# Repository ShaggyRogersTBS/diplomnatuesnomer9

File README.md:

# Дипломен Проект
Разработка на метеорологична система с уеб приложение и устройство на базата на ESP32, което измерва метеорологични стойности и ги записва в база данни, откъде после те са достъпни чрез уеб приложение

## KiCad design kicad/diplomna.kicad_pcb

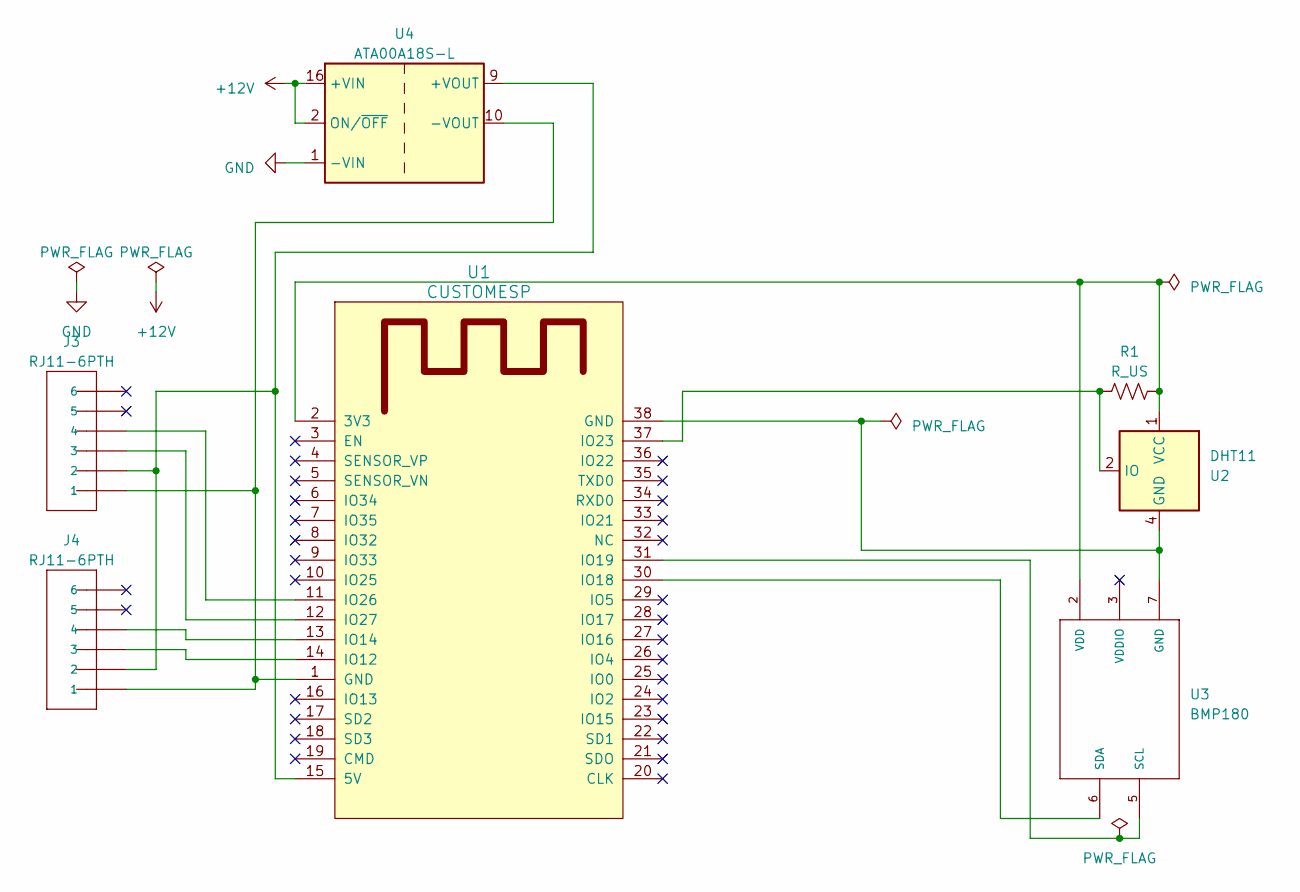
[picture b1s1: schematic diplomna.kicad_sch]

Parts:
J3, J4: RJ11-6PTH; RJ11-6
R1: R_US; R_Axial_DIN0204_L3.6mm_D1.6mm_P2.54mm_Vertical
U1: CUSTOMESP; ESP32-WROOM
U2: DHT11; Aosong_DHT11_5.5x12.0_P2.54mm
U3: BMP180
U4: ATA00A18S-L; Converter_DCDC_Artesyn_ATA_SMD

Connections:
+12V: U4.2 (ON/~OFF), U4.16 (+VIN)
GND: U4.1 (-VIN)
unnamed: R1.2, U1.2 (3V3), U2.1 (VCC), U3.2 (VDD)
unnamed: J3.2, J4.2, U1.15 (5V), U4.9 (+VOUT)
unnamed: J4.3, U1.14 (IO12)
unnamed: J4.4, U1.13 (IO14)
unnamed: U1.30 (IO18), U3.6 (SDA)
unnamed: U1.31 (IO19), U3.5 (SCL)
unnamed: R1.1, U1.37 (IO23), U2.2 (IO)
unnamed: J3.4, U1.11 (IO26)
unnamed: J3.3, U1.12 (IO27)
unnamed: U1.38 (GND), U2.4 (GND), U3.7 (GND)
unnamed: J3.1, J4.1, U1.1 (GND), U4.10 (-VOUT)

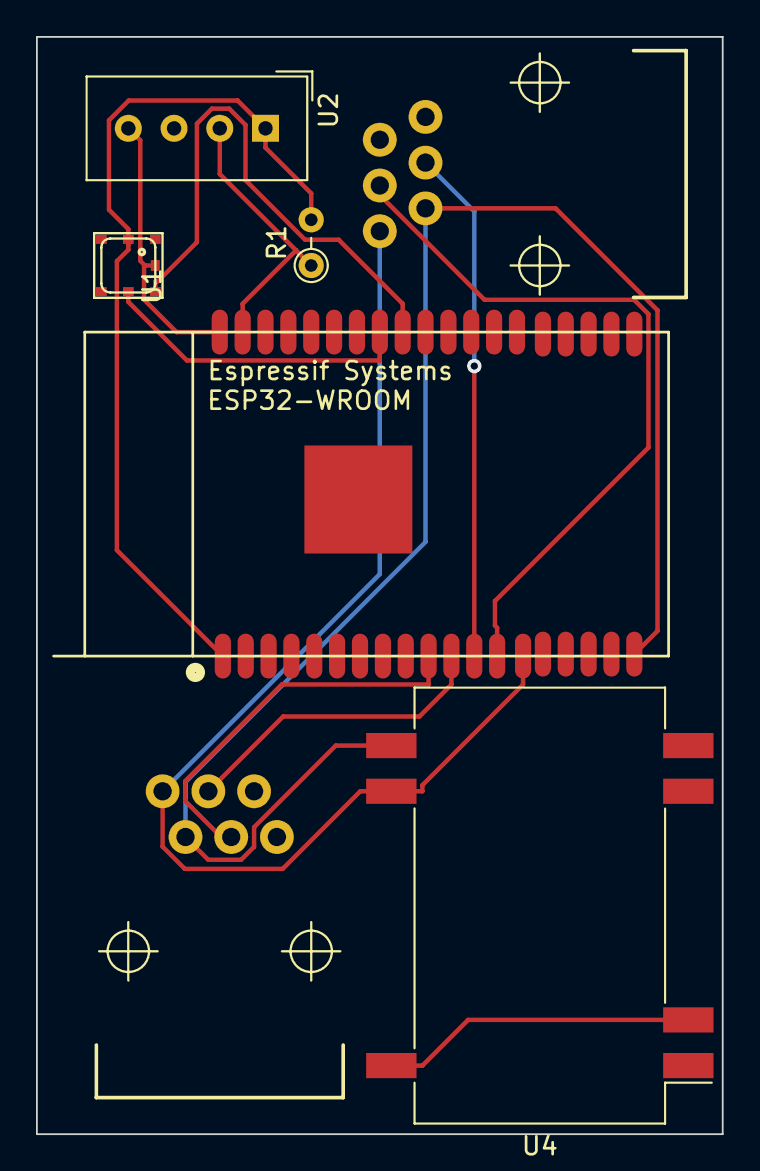
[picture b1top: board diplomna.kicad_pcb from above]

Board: 2 copper layers, 38.1 x 61.0 mm, 7 parts (0 on the bottom side), 12 nets.

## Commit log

2023-02-20 Main Page That Redirects to the next page.
2023-02-20 Rename index.php to website/index.php
2023-02-20 Rename styles.css to website/styles.css
2023-02-20 Create foldermaker
2023-02-21 css for the tables page + bootstrap install
    background photo upload
2023-03-05 added wind_direction
2023-03-05 Rename test.c to main.c
2023-03-05 wind speed query
2023-03-06 Rename diplomna.dsn to kicad/diplomna.dsn
2023-03-06 kicad pcb + schematic files
    no libraries !!!!
2023-03-07 Create httprequestsql
2023-03-07 support for wind speed, wind direction, humidity
2023-03-07 support for barometric pressure
2023-03-07 support for http request
    Промяна на void loop функцията, която качва нещата към сървъра. Промяната първо изпраща информацията на уеб сървъра, а след това уеб сървъра я записва на MariaDB сървъра
2023-03-07 removed support for mariadb sql upload
2023-03-07 add/remove support
    Премахнато измерване на валежи
    Добавено измерване на атмосферно налягане
2023-03-07 bug fixes
2023-03-07 Rename httprequestsql to phpscript.php
2023-03-08 HTTP GET to HTTP POST
2023-03-08 update get to post request http
2023-03-08 bug fix
    bug fix + komentari
2023-03-08 wind speed support
    added windspeed support
2023-03-13 for replace
2023-03-13 documentation
2023-05-30 1/2 final
    1/2 final
2023-05-30 Rename test.ino to main.ino
